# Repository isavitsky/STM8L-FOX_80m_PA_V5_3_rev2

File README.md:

# STM8L-FOX_80m_PA_V5_3_rev2
STM8L 80m fox power amplifier board schematics and PCB version 5.3 revision 2

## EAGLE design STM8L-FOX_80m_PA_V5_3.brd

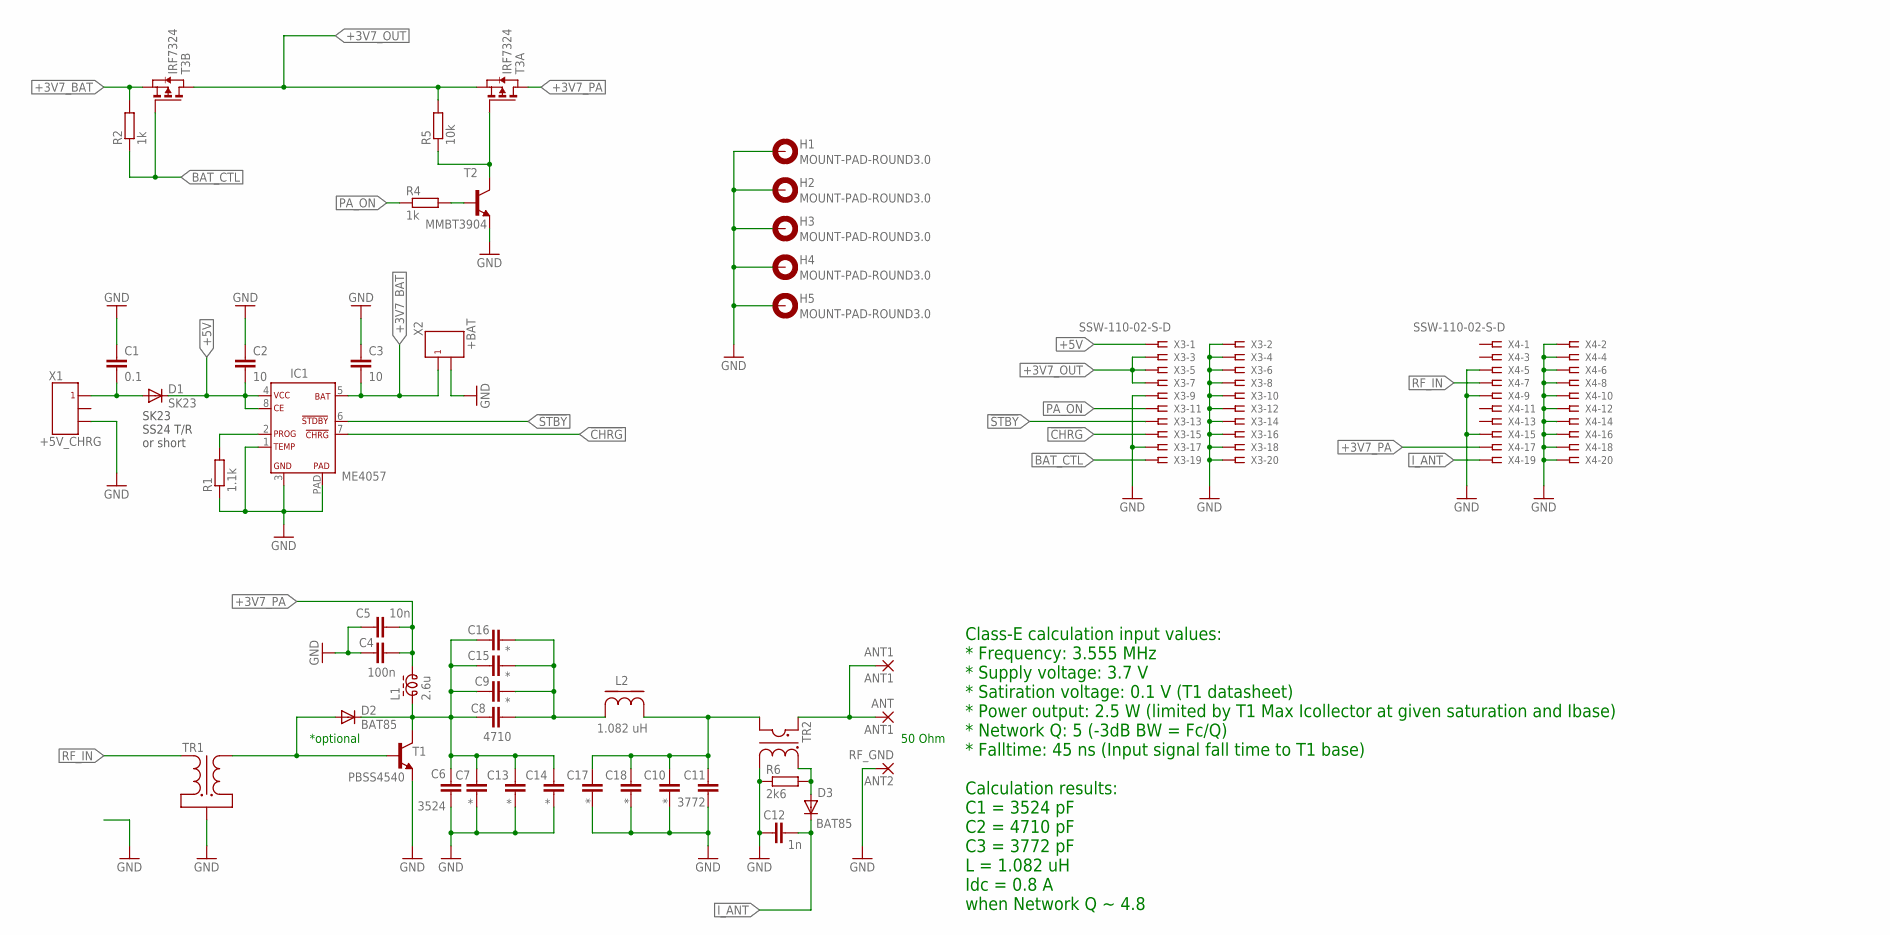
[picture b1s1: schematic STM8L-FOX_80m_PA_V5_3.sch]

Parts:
ANT, ANT1: ANT1; 2,54/0,8
C1: 0.1; C1206K
C2, C3: 10; C1206K
C4: 100n; C1206K
C5: 10n; C1206K
C6: 3524; C1206K
C7, C9, C10, C13, C14, C15, C16, C17, C18: *; C1206K
C8: 4710; C1206K
C11: 3772; C1206K
C12: 1n; C1206K
D1: SK23; DO-214AC
D2, D3: BAT85; DO34-7
H1, H2, H3, H4, H5: MOUNT-PAD-ROUND3.0; 3,0-PAD
IC1: ME4057A; SOP08-PP
L1: 2.6u; ZD6-3W
L2: 1.082 uH; T68_COIL
R1: 1.1k; R1206
R2, R4: 1k; R1206
R5: 10k; R1206
R6: 2k6; R1206
RF_GND: ANT2; 2,54/0,8
T1: PBSS4540; SOT223
T2: MMBT3904; SOT23-BEC
T3: IRF7324; SO8
TR1: K7X4X2_TRANS_1V1
TR2: K7X4X2_TRANS_CURRENT
X1: +5V_CHRG; A2501WR-3P
X2: +BAT; A2501WR-2P
X3, X4: SSW-110-02-S-D

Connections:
!CHRG!: IC1.7, X3.15
!STBY!: IC1.6, X3.13
+3V7_BAT: C3.2, IC1.5, R2.2, T3.3 (S), X2.P$1
+3V7_OUT: R5.2, T3.1 (S), T3.5 (D), T3.6 (D), X3.3, X3.5, X3.7
+3V7_PA: C4.2, C5.1, L1.2, T3.7 (D), T3.8 (D), X4.17
+5V: C2.2, D1.C, IC1.4, IC1.8, X3.1
BAT_CTL: R2.1, T3.4 (G), X3.19
CHRGR: C1.2, D1.A, X1.P$1
GND: C1.1, C2.1, C3.1, C4.1, C5.2, C6.2, C7.2, C10.2, C11.2, C12.1, C13.2, C14.2, C17.2, C18.2, H1.B3,0, H2.B3,0, H3.B3,0, H4.B3,0, H5.B3,0, IC1.1, IC1.3, IC1.PAD, R1.1, R6.1, RF_GND.1, T1.3 (E), T2.E, TR1.P$1, TR2.P$4, X1.P$3, X2.P$2, X3.2, X3.4, X3.6, X3.8, X3.9, X3.10, X3.12, X3.14, X3.16, X3.17, X3.18, X3.20, X4.2, X4.4, X4.5, X4.6, X4.8, X4.9, X4.10, X4.12, X4.14, X4.15, X4.16, X4.18, X4.20
I_ANT: C12.2, D3.C, X4.19
unnamed: D2.A, T1.1 (B), TR1.P$3
unnamed: R5.1, T2.C, T3.2 (G)
unnamed: C8.2, C9.2, C15.2, C16.2, L2.P$1
unnamed: IC1.2, R1.2
unnamed: R4.2, T2.B
unnamed: C6.1, C7.1, C8.1, C9.1, C13.1, C14.1, C15.1, C16.1, D2.C, L1.1, T1.2 (C), T1.4 (C)
unnamed: C10.1, C11.1, C17.1, C18.1, L2.P$2, TR2.P$2
unnamed: ANT.1, ANT1.1, TR2.P$1
unnamed: D3.A, R6.2, TR2.P$3
PA_ON: R4.1, X3.11
RF_IN: TR1.P$2, X4.7

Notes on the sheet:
SK23 SS24 T/R or short
*optional
Class-E calculation input values: * Frequency: 3.555 MHz * Supply voltage: 3.7 V * Satiration voltage: 0.1 V (T1 datasheet) * Power output: 2.5 W (limited by T1 Max Icollector at given saturation and Ibase) * Network Q: 5 (-3dB BW = Fc/Q) * Falltime: 45 ns (Input signal fall time to T1 base) Calcul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
50 Ohm

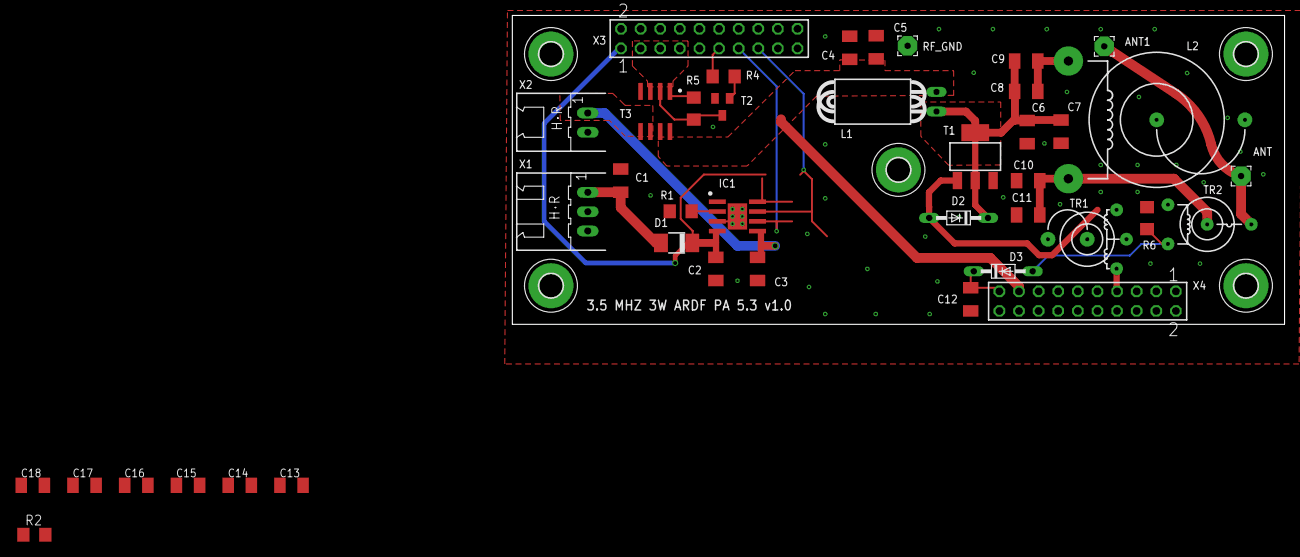
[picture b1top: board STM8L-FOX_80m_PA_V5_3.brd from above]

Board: 2 copper layers, 100.0 x 40.0 mm, 46 parts (0 on the bottom side), 21 nets.
